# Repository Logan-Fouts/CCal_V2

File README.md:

Contrib Cal v2 is a contribution tracker built around a Raspberry Pi Zero W. It shows your GitHub activity using LEDs and includes a web interface for easy setup and control. The project is open, hackable, and designed for anyone interested in building their own contribution calendar.

Take a look at my [website!](https://www.contrib-cal.com/)

## Availability
This will soon be available to purchase as a kit from sellers like Elecrow and Tindie!

---

## Sponsored by PCBWay

PCBWay provided the PCBs for this project. They offer PCB fabrication and 3D printing with quick turnaround and worldwide shipping.  
[Check out PCBWay.com](https://pcbway.com) if you want to order your own boards.

---

## Features

- **GitHub Sync:** Shows your GitHub activity on an LED matrix.
- **Weather Animations:** Displays weather effects and temperature.
- **Tailscale:** Optionally connect your Pi to a Tailscale network.
- **Syncthing:** Optionally run a Syncthing node for file sync.
- **Pi-hole:** Optionally run Pi-hole for ad blocking.
- **Customizable:** Animations and logic are written in Python.
- **DIY Build:** Use a 3D-printed case and a custom PCB LED matrix.
- **Web Interface:** Configure settings and add-ons from your browser.

---

## Hardware Files

- **3D Print Files:** Available on Thingiverse at [https://www.thingiverse.com/thing:7136260](https://www.thingiverse.com/thing:7136260)
- **KiCad PCB Design Files:** Located in the `KiCad` folder in this repository.
- **PCBWay Order Zip:** The `PCBWay file.zip` in this repo can be uploaded directly to PCBWay—just drag and drop it on their site to order your board.

---

## Web Interface

You can manage most settings and add-ons through a simple web page hosted on the Pi.

---

## Build Guide

- **LEDs:** 28x SMD5050 RGB addressable LEDs (SK6812 or similar)
- **Microcontroller:** 1x Raspberry Pi Zero W (Pi Zero 2 W may work, but not tested)
- **Power Adapter:** 5V step down buck convertor and usbc breakout board
- **PCB:** Can be ordered using the `PCBWay file.zip` mentioned previosly

You can substitute

---

## Getting Started

See [GettingStarted.md](./GettingStarted.md) for step-by-step instructions on flashing, setup, and configuration.

---

## Contributing

Pull requests and suggestions are welcome.  
If you run into issues or have ideas, feel free to open an issue on GitHub.

---

## Note on GitHub API Real-Time Updates

Contrib Cal v2 displays your GitHub activity as close to real-time as possible using the GitHub API. However, there may be delays in showing the most recent events due to how quickly GitHub updates and provides new event data. This is a limitation of the GitHub API itself and not an issue with this project's implementation.

---

Thanks for checking out Contrib Cal, Feel free to open up PRs!

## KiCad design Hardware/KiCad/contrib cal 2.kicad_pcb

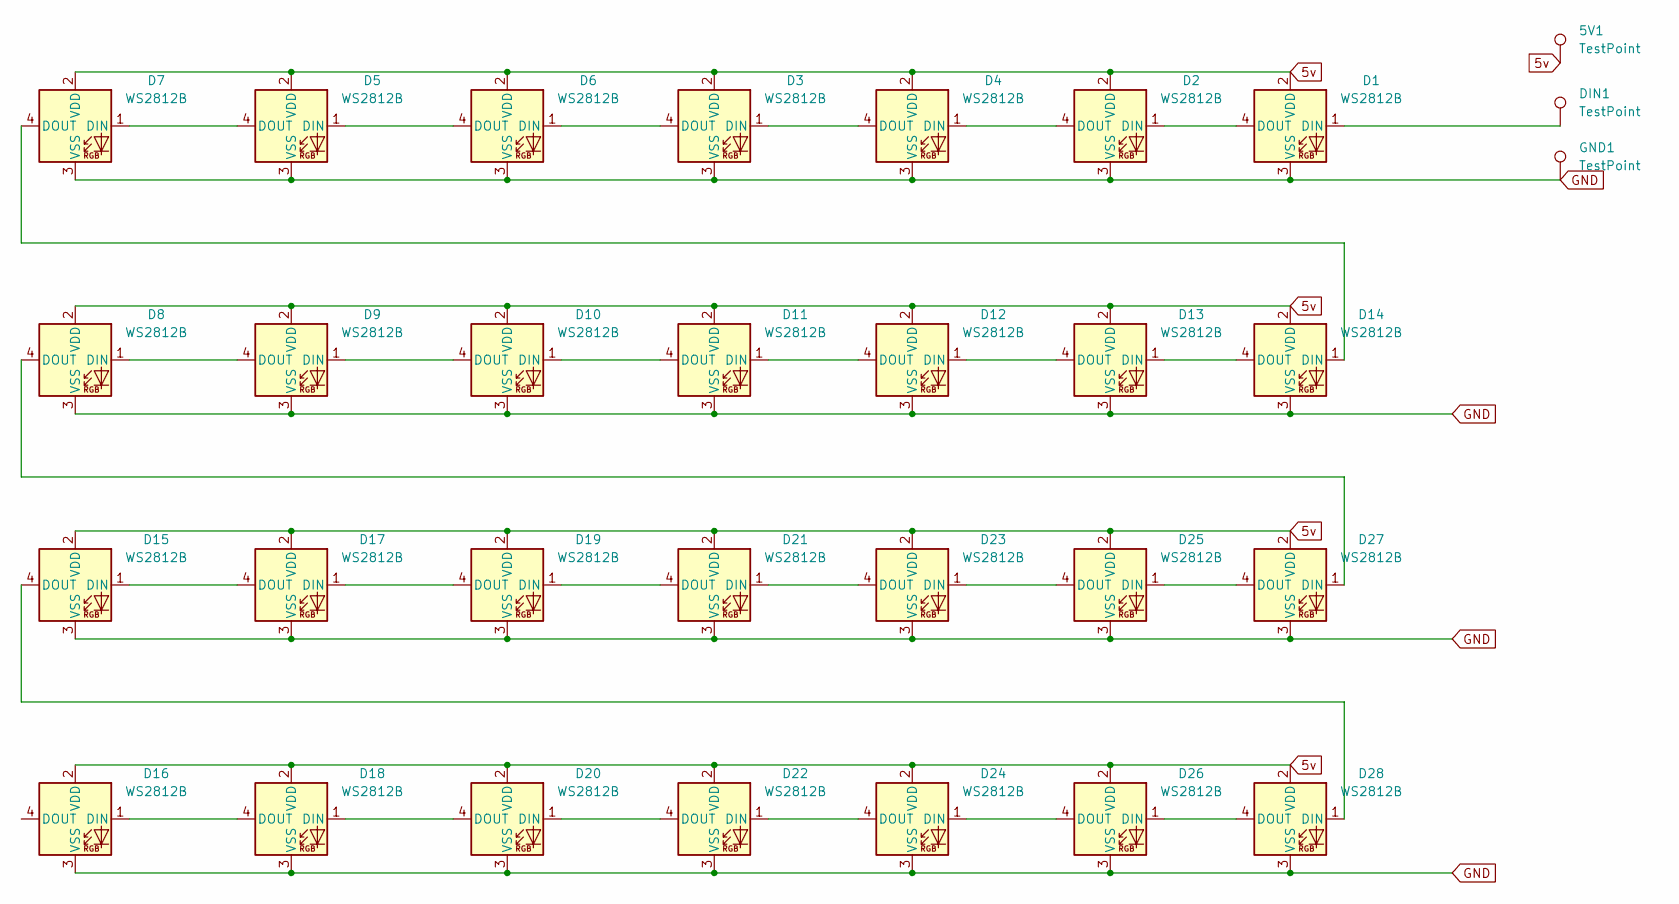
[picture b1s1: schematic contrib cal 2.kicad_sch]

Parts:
5V1: TestPoint; TestPoint_Pad_3.0x3.0mm
D1, D2, D3, D4, D5, D6, D7, D8, D9, D10, D11, D12, D13, D14, D15, D16, D17, D18, D19, D20, D21, D22, D23, D24, D25, D26, D27, D28: WS2812B; WS2812
DIN1: TestPoint; TestPoint_Pad_3.0x3.0mm
GND1: TestPoint; TestPoint_Pad_3.0x3.0mm

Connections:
5v: 5V1.1, D1.2 (VDD), D2.2 (VDD), D3.2 (VDD), D4.2 (VDD), D5.2 (VDD), D6.2 (VDD), D7.2 (VDD), D8.2 (VDD), D9.2 (VDD), D10.2 (VDD), D11.2 (VDD), D12.2 (VDD), D13.2 (VDD), D14.2 (VDD), D15.2 (VDD), D16.2 (VDD), D17.2 (VDD), D18.2 (VDD), D19.2 (VDD), D20.2 (VDD), D21.2 (VDD), D22.2 (VDD), D23.2 (VDD), D24.2 (VDD), D25.2 (VDD), D26.2 (VDD), D27.2 (VDD), D28.2 (VDD)
GND: D1.3 (VSS), D2.3 (VSS), D3.3 (VSS), D4.3 (VSS), D5.3 (VSS), D6.3 (VSS), D7.3 (VSS), D8.3 (VSS), D9.3 (VSS), D10.3 (VSS), D11.3 (VSS), D12.3 (VSS), D13.3 (VSS), D14.3 (VSS), D15.3 (VSS), D16.3 (VSS), D17.3 (VSS), D18.3 (VSS), D19.3 (VSS), D20.3 (VSS), D21.3 (VSS), D22.3 (VSS), D23.3 (VSS), D24.3 (VSS), D25.3 (VSS), D26.3 (VSS), D27.3 (VSS), D28.3 (VSS), GND1.1
unnamed: D1.1 (DIN), DIN1.1
unnamed: D1.4 (DOUT), D2.1 (DIN)
unnamed: D2.4 (DOUT), D4.1 (DIN)
unnamed: D3.1 (DIN), D4.4 (DOUT)
unnamed: D3.4 (DOUT), D6.1 (DIN)
unnamed: D5.1 (DIN), D6.4 (DOUT)
unnamed: D5.4 (DOUT), D7.1 (DIN)
unnamed: D8.1 (DIN), D9.4 (DOUT)
unnamed: D10.1 (DIN), D11.4 (DOUT)
unnamed: D9.1 (DIN), D10.4 (DOUT)
unnamed: D11.1 (DIN), D12.4 (DOUT)
unnamed: D12.1 (DIN), D13.4 (DOUT)
unnamed: D13.1 (DIN), D14.4 (DOUT)
unnamed: D7.4 (DOUT), D14.1 (DIN)
unnamed: D15.1 (DIN), D17.4 (DOUT)
unnamed: D15.4 (DOUT), D28.1 (DIN)
unnamed: D16.1 (DIN), D18.4 (DOUT)
unnamed: D17.1 (DIN), D19.4 (DOUT)
unnamed: D18.1 (DIN), D20.4 (DOUT)
unnamed: D19.1 (DIN), D21.4 (DOUT)
unnamed: D20.1 (DIN), D22.4 (DOUT)
unnamed: D21.1 (DIN), D23.4 (DOUT)
unnamed: D22.1 (DIN), D24.4 (DOUT)
unnamed: D23.1 (DIN), D25.4 (DOUT)
unnamed: D24.1 (DIN), D26.4 (DOUT)
unnamed: D25.1 (DIN), D27.4 (DOUT)
unnamed: D26.1 (DIN), D28.4 (DOUT)
unnamed: D8.4 (DOUT), D27.1 (DIN)

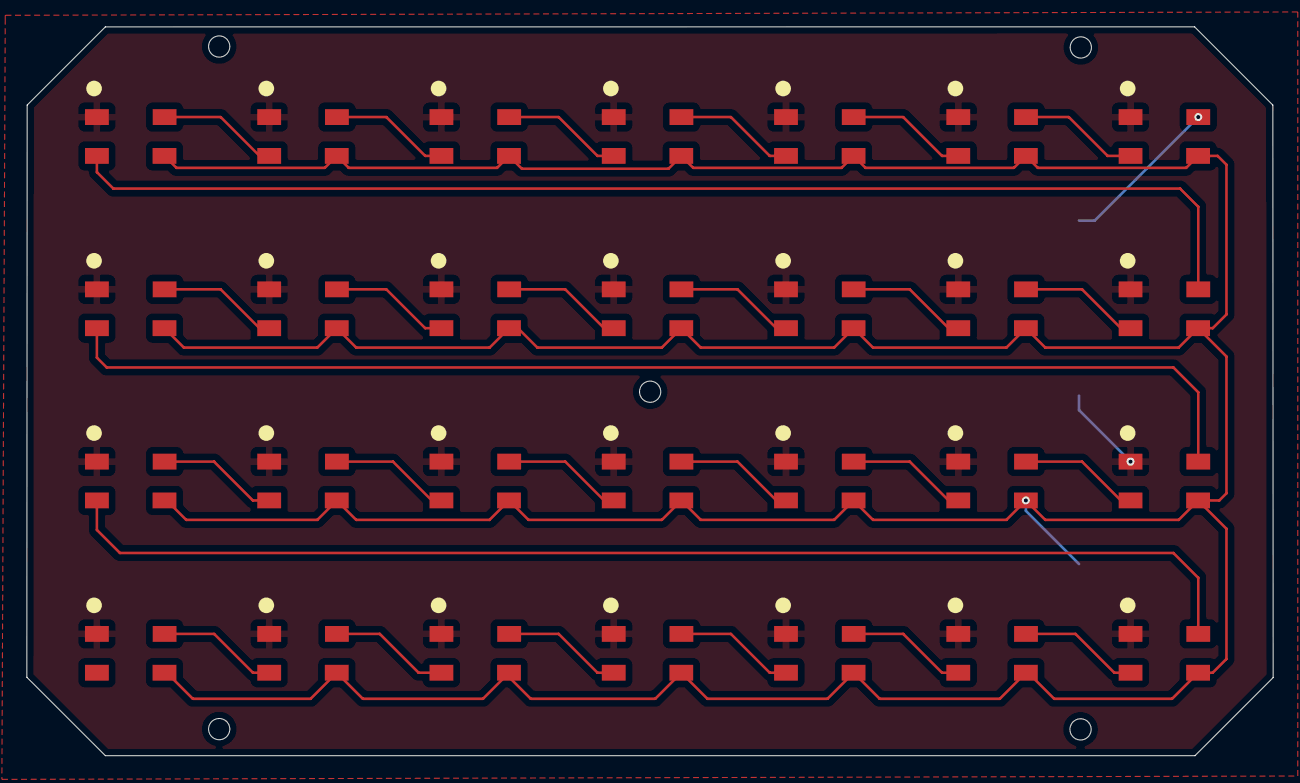
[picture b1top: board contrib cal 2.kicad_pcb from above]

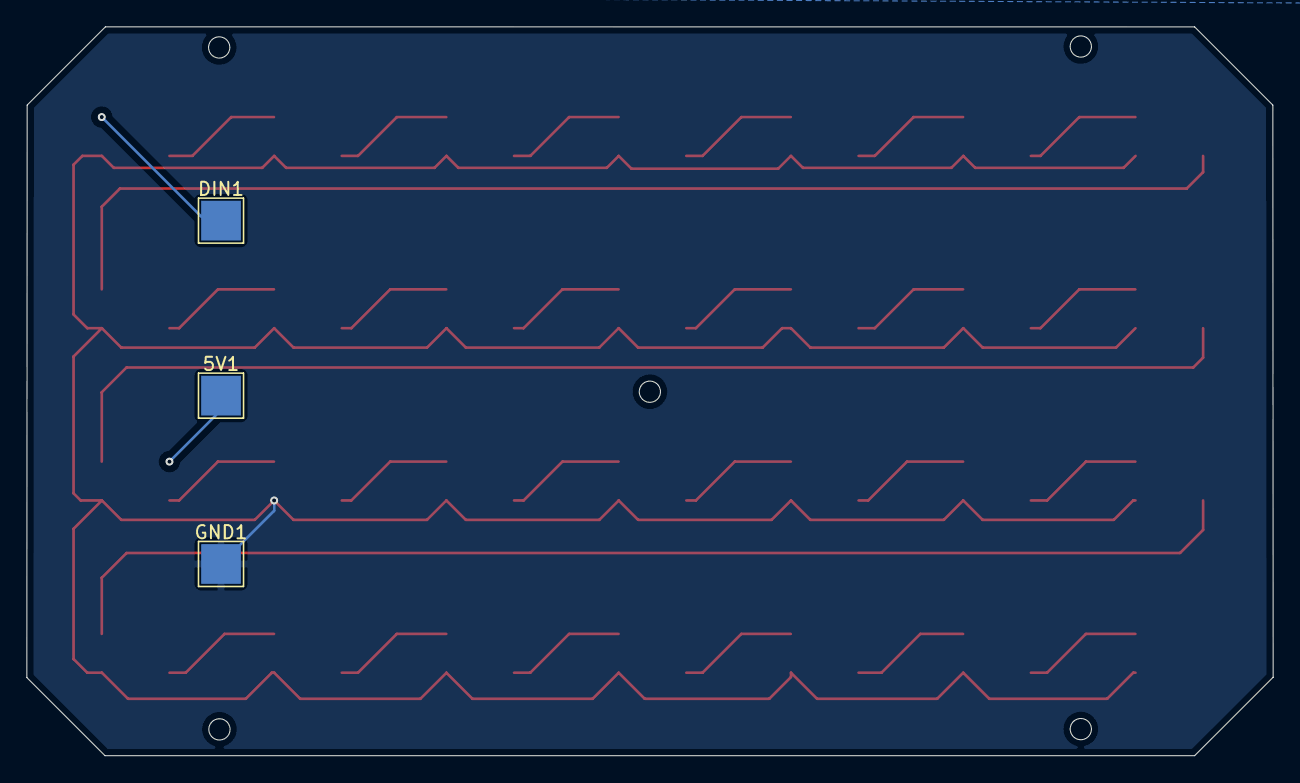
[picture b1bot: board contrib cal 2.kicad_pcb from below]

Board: 2 copper layers, 94.1 x 55.0 mm, 31 parts (3 on the bottom side), 30 nets.

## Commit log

2025-06-25 init
2025-06-27 Gui start
2025-06-27 Web GUI Config and led control rewrite start
2025-06-27 update gitignore
2025-06-27 Add setup script for add-ons and integrate with config submission
2025-06-27 addon script simplification
2025-06-27 update to use correct config for led controls
2025-06-28 systemd services setup and some clean ups
2025-06-28 forgot to add unit files in previous commit
2025-06-28 setup script start
2025-06-28 reduce sleep duration in main loop to 1 minute for more frequent LED updates. New readme
2025-06-29 little fixes
2025-07-01 fixes
2025-07-02 update setup
2025-07-03 setup nicer
2025-07-03 more addons setup
2025-07-03 tailscale fixes
2025-07-03 setup
2025-07-03 more updates
2025-07-03 enhance service info output in .bashrc for better readability
2025-07-03 final
2025-07-03 quick update
2025-07-03 Add new event fetching and flashing functionality to GitHub tracker and LED utilities
2025-07-03 Fix indentation for event checking in main loop
2025-07-04 main cleanup and readme update
2025-07-07 weather tracking and animations start
2025-07-07 Api start and led update optimizations
2025-07-10 Add LED display for temperature and enhance weather tracking functionality
2025-07-12 brightness cleanup and reorg
2025-07-12 animation length weirdness fix
2025-07-13 minor changes
2025-08-05 update setup and some cleanup
2025-08-25 Bulletproofing
2025-08-26 Cleanup work
2025-08-27 Update get started
2025-08-29 Bulletproofing and testing
2025-08-29 Enhance Getting Started guide and README for clarity; update WebGUI scripts for improved user experience and authentication
2025-08-29 Add .env file creation and user credentials setup for WebGUI
2025-08-29 Add temporary password setup for Pi-hole installation
2025-08-29 Clarify instructions for locating the WiFi configuration file in the Getting Started guide
2025-08-29 Clarify instructions for configuring the device in the Getting Started guide
2025-08-29 Add call to setup_addons.sh in setup script
2025-08-29 Enhance Getting Started guide with additional notes on first boot duration and setup instructions
2025-08-29 Fix setup script to use sudo for Pi-hole password setup and run setup_addons.sh with proper command
2025-08-29 Add config.json creation before running setup_addons.sh
2025-08-29 Remove unnecessary sourcing of .bashrc after running setup_addons.sh
2025-08-29 Add instructions to source updated bashrc after running setup script
2025-08-29 Refactor startup animation settings to use a dropdown menu and enhance modal styling with improved responsiveness and visual effects
2025-08-29 Fix config file path in CONFIG_MANAGER and update USERNAME variable in main.py
2025-08-30 Improve pip installation process in setup.sh to handle --break-system-packages option conditionally
2025-09-02 Refactor LED brightness handling and update GUI to include brightness input
2025-09-02 Enhance Syncthing setup with improved connection instructions and enable unattended upgrades
2025-09-02 Add handling to skip LED updates when brightness is set to 0
2025-09-04 Disable unnecessary services to speed up boot time
2025-09-04 Added in hardware files and updated readme
2025-09-04 reformat read me
2025-09-09 Add time-based condition to skip LED updates and define ON_TIME/OFF_TIME constants
2025-09-09 Add ON_TIME and OFF_TIME configuration options for LED control
2025-09-09 Add example configuration file with initial settings
2025-09-11 Refactor animation color values and adjust rainbow cycle speed for improved visual effects
2025-09-15 Add unit tests for LED control, weather tracking, and GitHub event handling; refactor setup script
2025-09-15 Refactor hardcoded username to a placeholder in main.py, server.js, and setup_addons.sh for improved configurability
2025-09-15 testing and linting clean up. Needs hardware integration testing before merge to main
2025-09-15 Update username var for sed in setup
2025-09-15 Refactor GithubTracker initialization to accept config_file parameter and update event fetch limit
2025-09-16 Enhance setup instructions in GettingStarted.md
2025-09-16 Update setup instructions and server configuration for CCal
    - Revised GettingStarted.md to remove version references and clarify setup steps.
    - Changed server.js to run on port 80 instead of 8080.
    - Enhanced setup.sh to prompt for WebGUI username and password, allowing user-defined credentials.
2025-09-16 Remove brightness parameter from sun_animation_loop call in LedUtils
2025-09-16 Update server port to 8080 and adjust access URL in setup instructions
2025-09-16 Add comment to clarify USERNAME variable usage for setup script
2025-09-16 Remove title from README
2025-09-16 Tuen off leds during specific times
2025-09-16 Fix digit pattern for number 3 in led_utils.py
2025-09-16 Enhance LED animations and add weather tracker tests
    - Updated snow animation colors to use GRB order for consistency.
    - Improved fog animation with gradient effects and multiple moving patches.
    - Refactored brightness handling in snow and rain animations.
    - Added unit tests for WeatherTracker, covering various scenarios including cache handling and API requests.
2025-09-16 Enhance theater chase animation and update LED demo script
2025-09-16 Refine LED control logic to respect on_time and off_time settings
2025-09-18 Add demo script for LED control and comprehensive tests for WeatherTracker
    - Created a demo script (led_demo.py) showcasing number display, color fills, and various animations using LedUtils.
    - Implemented unit tests for WeatherTracker, covering weather updates, API requests, and cache management.
    - Added mock data and methods to simulate API responses and test error handling in weather requests.
2025-09-18 remove unneeded 3d files
2025-09-18 Update main to rtl commits
2025-09-18 Starting potential rewrite - Want to make it easier to understand for users who wish to modify the code
2025-09-18 Weather Tracker -Reimplemeted and bullet proofed hopefully with TDD
2025-09-18 Add GitHubTracker integration module and unit tests
2025-09-19 Add ConfigManager and GitHubTracker integration with tests
    - Implement ConfigManager for managing configuration settings.
    - Update GitHubTracker to enforce parameter validation.
    - Add unit tests for ConfigManager functionality.
    - Include new GitHubTracker integration module.
2025-09-19 Refactor LED control and animation modules with comprehensive tests
    - Implemented AnimationRunner class for various LED animations.
    - Created LEDController class for low-level hardware interaction.
    - Added utility functions for color manipulation in led_utils.
    - Developed unit tests for AnimationRunner and LEDController.
    - Enhanced test coverage for utility functions in led_utils.
    - Introduced configuration management for GitHub and weather integrations.
2025-09-19 Add startup animation configuration and update setup script for editable install
2025-09-19 integration testing on pi
2025-09-19 Refactor weather tracker API URL and enhance LED display functionality for temperature indication
2025-09-19 Refactor LED control main script and GitHubTracker integration; update username handling in setup script
2025-09-19 Enhance animation handling and brightness control in LED updates
2025-09-19 Refactor LED control configuration and improve brightness handling; update setup script for correct directory paths
2025-09-19 Adjust minimum brightness threshold in calendar updates for improved visibility
2025-09-20 # Cleanup ## Did the following - Fixed brightness implementation for calandar - Added demo script to show possibilities
2025-09-23 Elecrow files
2025-09-23 updated bom and case obj
2025-09-23 organizing
2025-09-23 updated case obj
2025-10-09 update BOM
2025-12-28 Implement negative temperature handling in LED controller
    Add handling for negative temperature values with a specific color.
2025-12-28 Refactor Python dependency installation in setup.sh
    Updated Python installation process to handle different versions and added checks for pip installation. Modified the setup script to install Python dependencies globally with appropriate flags based 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
2025-12-29 Add Spotify integration and music visualization animation
2025-12-29 Refactor animation logic and clean up Spotify integration code
2026-01-07 Enhance Spotify integration with authentication setup and token management; update weather animation duration in demo
2026-01-07 fix indents
2026-01-08 Strava Integration work
2026-01-09 Add TODO services comments in main.py
    Added potential TODO services as comments.
2026-01-19 generic integration, removed spotify
2026-01-20 feat: Implement custom trackers feature with create, increment, delete, and color update functionalities
    - Added new endpoints for managing custom trackers in server.js
    - Updated index.ejs to include a new tab for custom trackers
    - Enhanced main.js to handle tracker loading, creation, and actions
    - Modified LeetCode.json and MusicPractice.json to reflect new data structures
    - Styled custom trackers section in style.css for better UI/UX
2026-01-20 fix: Adjust current day initialization and add metric field to tracker configurations
2026-01-27 integration runner loop update
2026-02-02 Refactor integration trackers to use a base class for common functionality and improve color handling
2026-02-02 Rename CCal to Daily Grid in various files and update service configurations
2026-02-02 Update paths and references to Daily Grid in configuration and documentation
2026-02-06 Update integration and configuration files to use placeholder USERNAME and improve error handling
